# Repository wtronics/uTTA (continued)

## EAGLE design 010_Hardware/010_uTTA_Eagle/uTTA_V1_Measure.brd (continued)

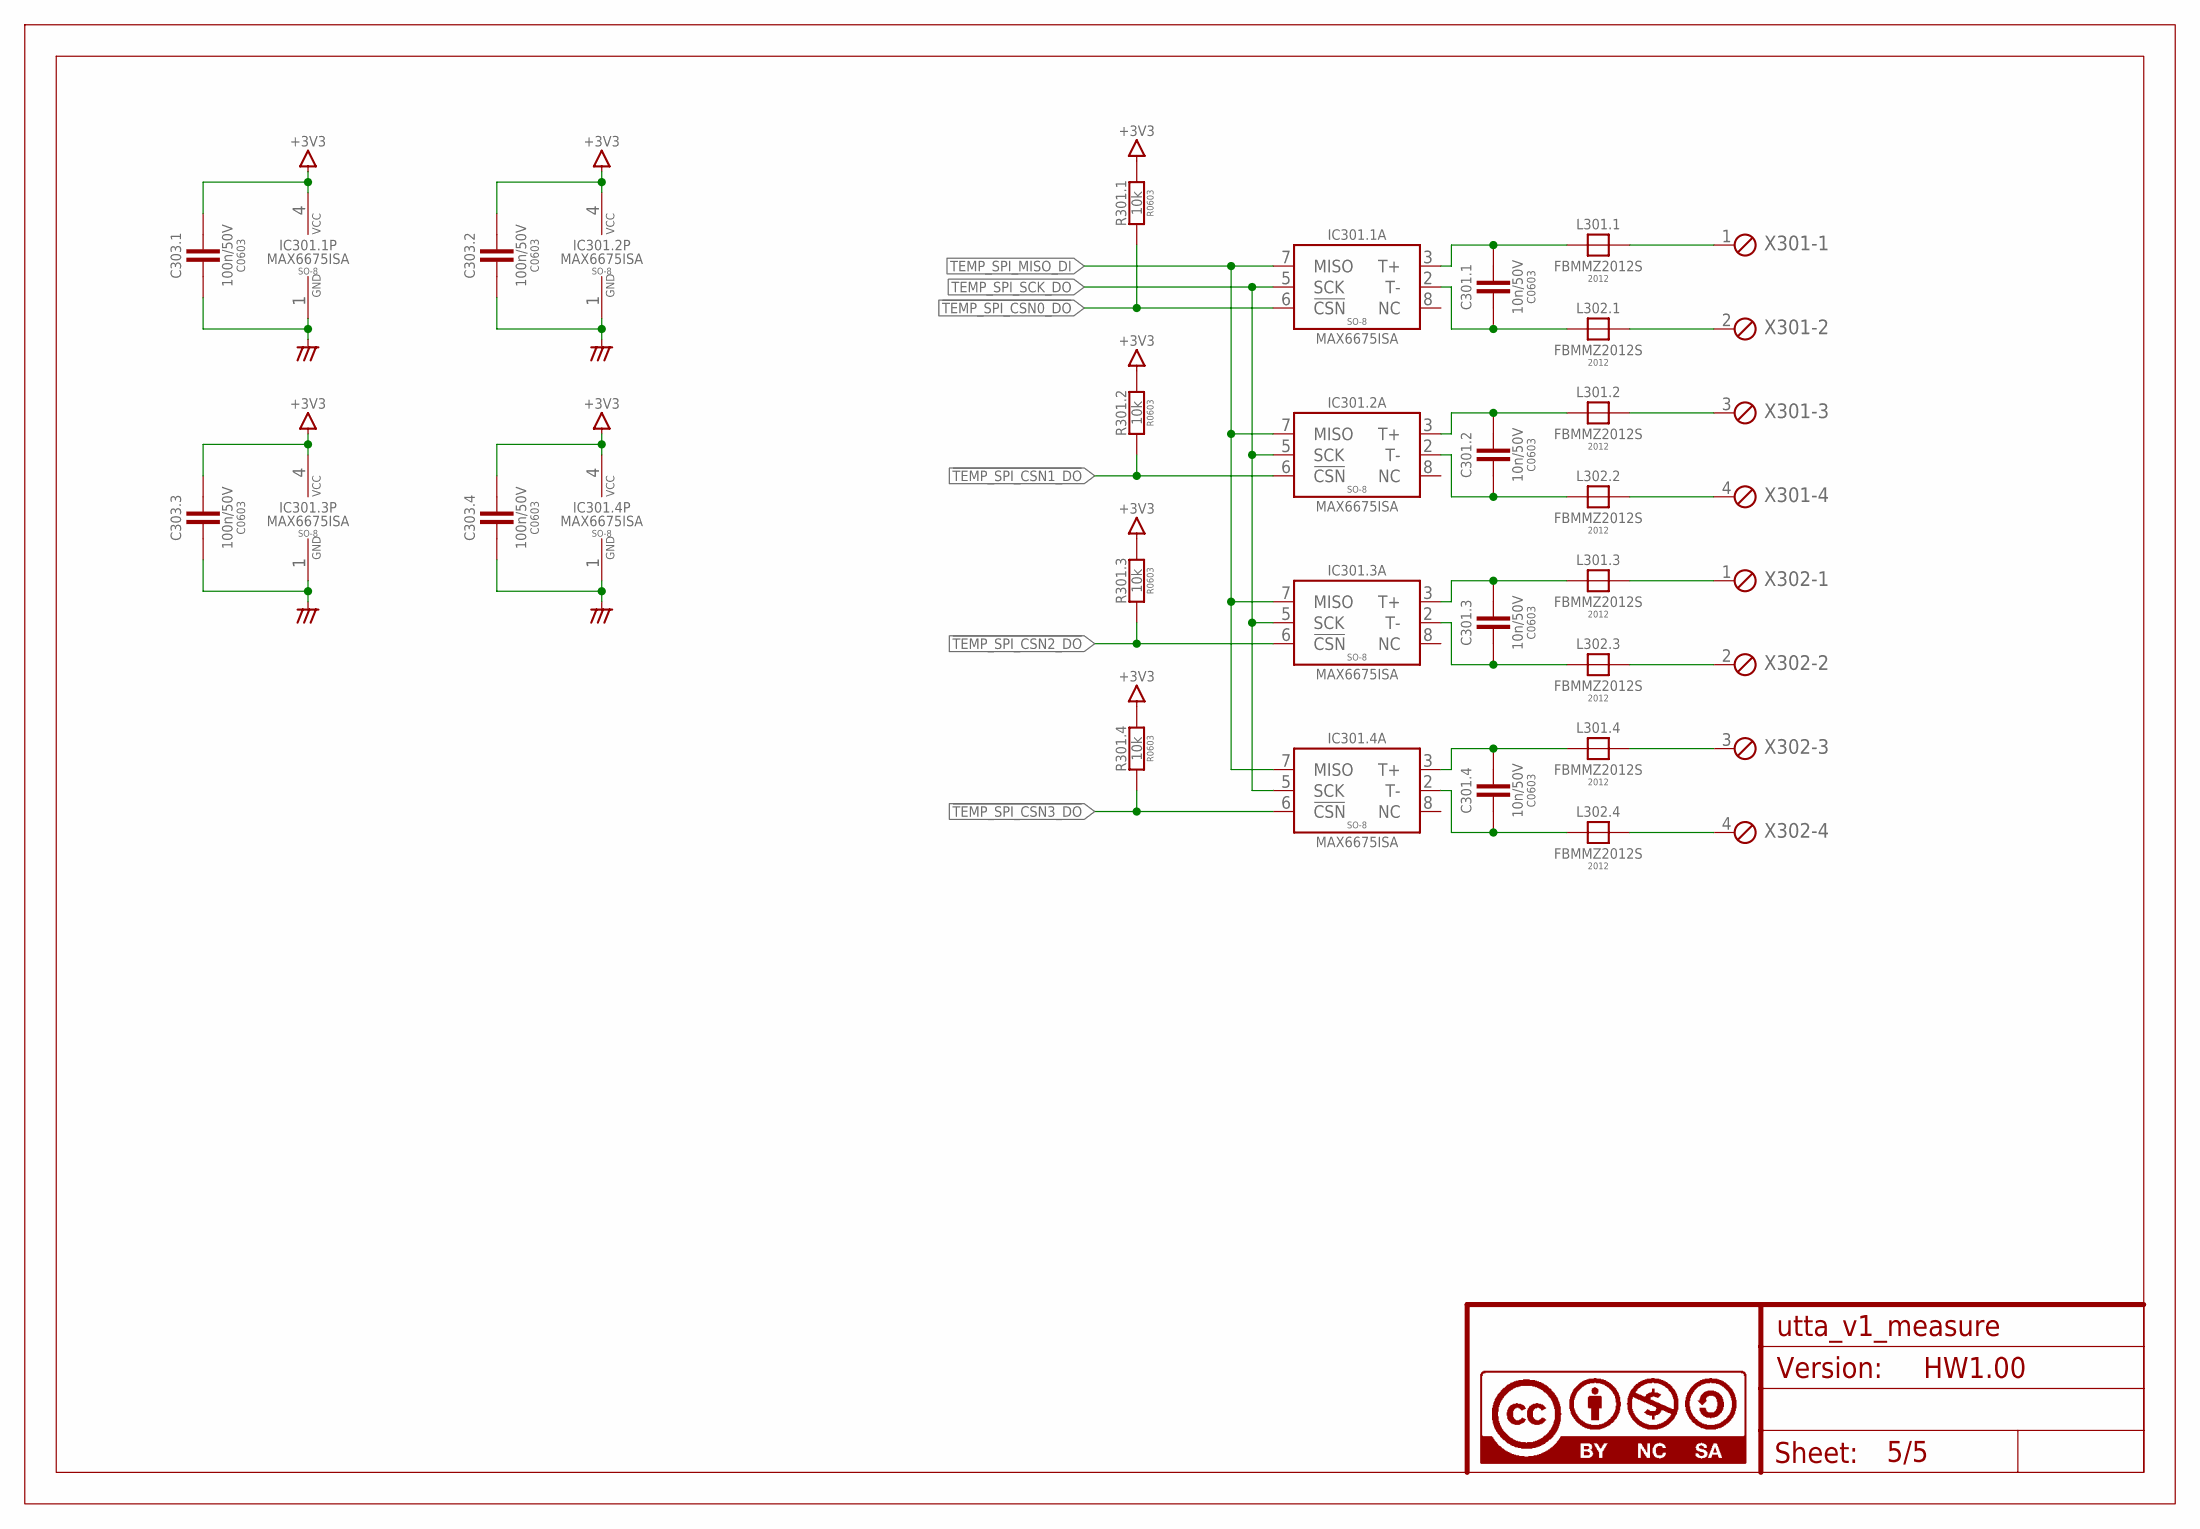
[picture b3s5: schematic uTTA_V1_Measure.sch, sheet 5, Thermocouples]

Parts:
C301.1, C301.2, C301.3, C301.4: 10n/50V; C0603
C303.1, C303.2, C303.3, C303.4: 100n/50V; C0603
IC301.1, IC301.2, IC301.3, IC301.4: MAX6675ISA; SO08
L301.1, L301.2, L301.3, L301.4, L302.1, L302.2, L302.3, L302.4: FBMMZ2012S; FB2012
R301.1, R301.2, R301.3, R301.4: 10k; R0603
U$9: A4L-LOC_CC_BY_NC_SA; A4_LOC_CC_BY_NC_SA
X301, X302: MPT4; 4POL254

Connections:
!TEMP_SPI_CSN0_DO: IC301.1.6 (!CSN), R301.1.2; also elsewhere on the board
!TEMP_SPI_CSN1_DO: IC301.2.6 (!CSN), R301.2.2; also elsewhere on the board
!TEMP_SPI_CSN2_DO: IC301.3.6 (!CSN), R301.3.2; also elsewhere on the board
!TEMP_SPI_CSN3_DO: IC301.4.6 (!CSN), R301.4.2; also elsewhere on the board
+3V3: C303.1.1, C303.2.1, C303.3.1, C303.4.1, IC301.1.4 (VCC), IC301.2.4 (VCC), IC301.3.4 (VCC), IC301.4.4 (VCC), R301.1.1, R301.2.1, R301.3.1, R301.4.1; also elsewhere on the board
AGND: C303.1.2, C303.2.2, C303.3.2, C303.4.2, IC301.1.1 (GND), IC301.2.1 (GND), IC301.3.1 (GND), IC301.4.1 (GND); also elsewhere on the board
TC1+: L301.1.2, X301.1
TC1-: L302.1.2, X301.2
TC2+: L301.2.2, X301.3
TC2-: L302.2.2, X301.4
TC3+: L301.3.2, X302.1
TC3-: L302.3.2, X302.2
TC4+: L301.4.2, X302.3
TC4-: L302.4.2, X302.4
TEMP_SPI_MISO_DI: IC301.1.7 (MISO), IC301.2.7 (MISO), IC301.3.7 (MISO), IC301.4.7 (MISO); also elsewhere on the board
TEMP_SPI_SCK_DO: IC301.1.5 (SCK), IC301.2.5 (SCK), IC301.3.5 (SCK), IC301.4.5 (SCK); also elsewhere on the board
TK1_N: C301.1.2, IC301.1.2 (T-), L302.1.1
TK1_P: C301.1.1, IC301.1.3 (T+), L301.1.1
TK2_N: C301.2.2, IC301.2.2 (T-), L302.2.1
TK2_P: C301.2.1, IC301.2.3 (T+), L301.2.1
TK3_N: C301.3.2, IC301.3.2 (T-), L302.3.1
TK3_P: C301.3.1, IC301.3.3 (T+), L301.3.1
TK4_N: C301.4.2, IC301.4.2 (T-), L302.4.1
TK4_P: C301.4.1, IC301.4.3 (T+), L301.4.1

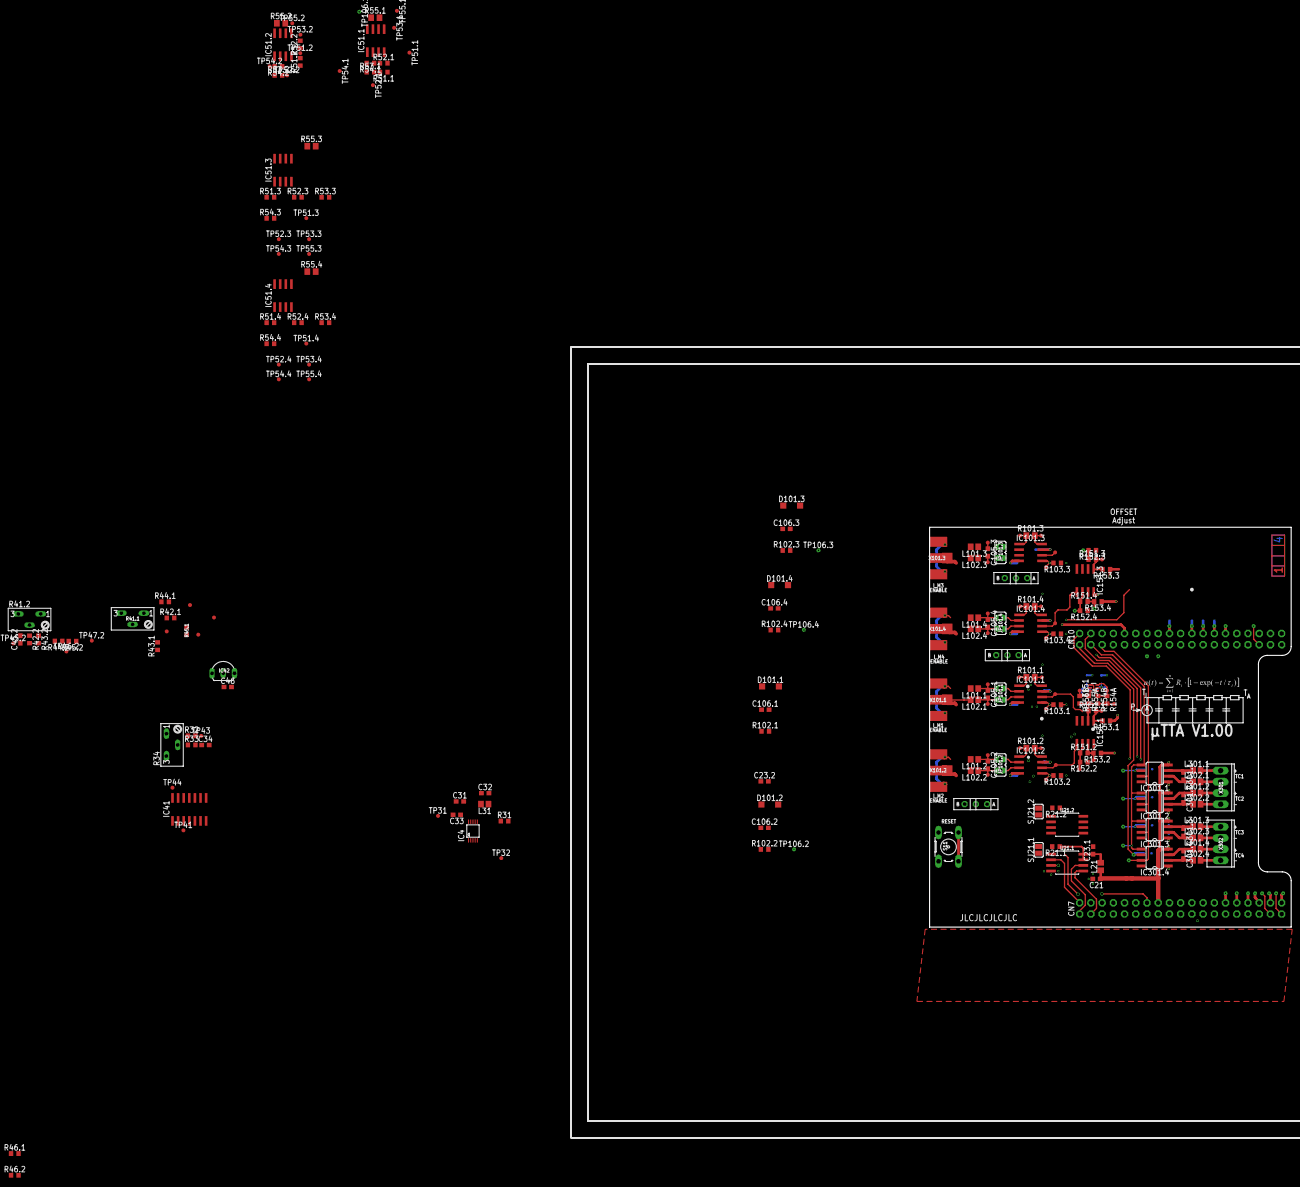
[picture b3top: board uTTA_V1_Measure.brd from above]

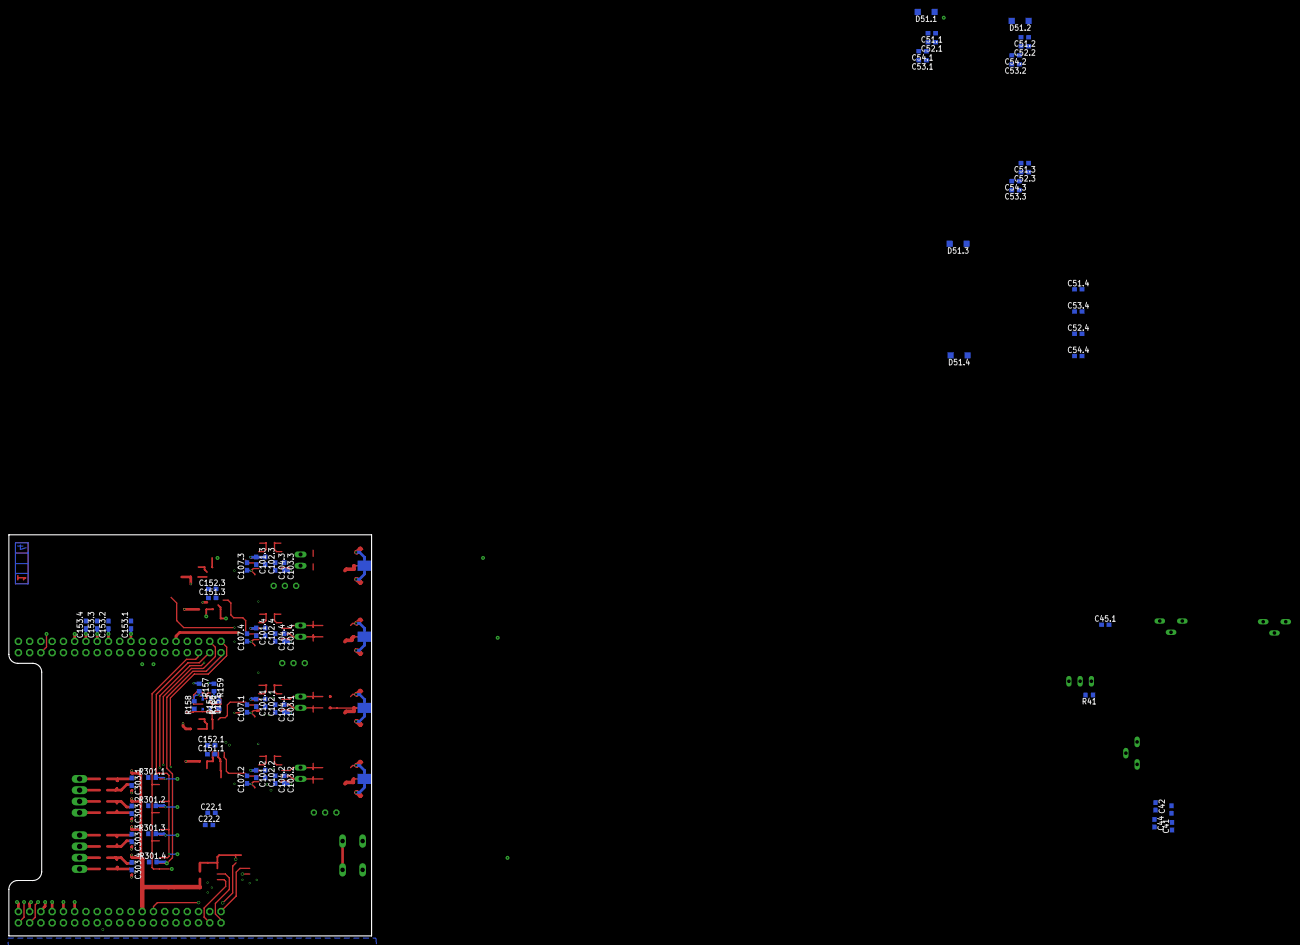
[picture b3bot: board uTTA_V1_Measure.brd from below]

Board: 4 copper layers, 81.8 x 90.5 mm, 313 parts (70 on the bottom side), 140 nets.

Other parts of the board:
U$1: A4_LOC_CC_BY_NC_SA

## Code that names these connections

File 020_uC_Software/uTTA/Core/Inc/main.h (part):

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

// Debug IO1 port
#define DBG_IO1_Pin LL_GPIO_PIN_0
#define DBG_IO1_GPIO_Port GPIOC
// Debug IO2 port
#define DBG_IO2_Pin LL_GPIO_PIN_1
#define DBG_IO2_GPIO_Port GPIOC
// Debug IO3 port
#define DBG_IO3_Pin LL_GPIO_PIN_2
#define DBG_IO3_GPIO_Port GPIOC
// Debug IO4 port
#define DBG_IO4_Pin LL_GPIO_PIN_3
#define DBG_IO4_GPIO_Port GPIOC
// Debug Pin for Sample time generation timer
#define TIM_DBG_PO_Pin LL_GPIO_PIN_10
#define TIM_DBG_PO_GPIO_Port GPIOA
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#define PWSTG_EN_DO_Pin LL_GPIO_PIN_0
#define PWSTG_EN_DO_GPIO_Port GPIOA
// Readback pin of powerstage power supply low
#define PWSTG_UVLO_DI_Pin LL_GPIO_PIN_1
#define PWSTG_UVLO_DI_GPIO_Port GPIOA
// Enable pin of external power supply
#define PSU_EN_DO_Pin LL_GPIO_PIN_4
#define PSU_EN_DO_GPIO_Port GPIOA
// Gate driver power supply enable
#define PWSTG_PWR_EN_DO_Pin LL_GPIO_PIN_0
#define PWSTG_PWR_EN_DO_GPIO_Port GPIOB


// Amplifier Gain Switching outputs
#define GAIN_B0_DO_Pin LL_GPIO_PIN_6
#define GAIN_B0_DO_GPIO_Port GPIOA
#define GAIN_B1_DO_Pin LL_GPIO_PIN_7
#define GAIN_B1_DO_GPIO_Port GPIOA


// Analog inputs for measurement
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#define PGA_DIODE2_AI_GPIO_Port GPIOB
#define PGA_DIODE1_AI_Pin LL_GPIO_PIN_11
#define PGA_DIODE1_AI_GPIO_Port GPIOB
#define CURR_MEAS_AI_Pin LL_GPIO_PIN_14
#define CURR_MEAS_AI_GPIO_Port GPIOB
#define PGA_DIODE4_AI_Pin LL_GPIO_PIN_15
#define PGA_DIODE4_AI_GPIO_Port GPIOB

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
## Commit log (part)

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2025-05-07 Added 6th parametre to SetChannelDescription for CalStatus
2025-05-07 Added Calibration Status to TSP Channels
2025-05-08 Removed dependency to OpenG Toolkit
2025-05-11 Added progress bar
2025-05-11 Update to latest import meta data format
2025-05-12 Added config define EARLY_HW_POWER_BOARD for older hardwares
2025-05-12 Improved localization for numeric conversion
2025-05-12 Improved progress bar behaviour
2025-05-12 Removed outdated parameter from function call
2025-05-12 Changed export setting
2025-05-12 Updated to latest importer return values structure
2025-05-12 Removed unused variables
2025-05-13 Added MetaValue for TSP_Calibration measurements
2025-05-13 Removed unused variable
2025-05-15 Update uTTA_umf_Viewer_GUI.py
    Changed from customtkinter to ttkbootstrap for better styling
    removed unused dependencies
2025-05-19 Fixed bug in state machine
2025-05-19 Added Calibration Measurement indicator flag
2025-05-19 Code Cleanup, added interpolation degrees as variable
2025-05-19 Added error handling for wrong files
2025-05-19 Tweaked file to be recognized as calibration measurement
2025-05-19 Another Try rescaling the window to a matching size
2025-05-26 Bugfix on FIle check
2025-06-13 Changed Frontend to ttkbootstrap
2025-06-13 Removed Customtkinter
2025-06-13 Removed linearization of thermocouple channel
2025-06-16 Updated Examples to latest umf-file version
2025-06-16 change general layout paradigma
2025-06-30 Delete uTTA_umf_Viewer.py
    Outdated because of umf Viewer GUI
2025-06-30 Update uTTA_data_import.py
    Minor bug fixing.
    Moved file selection and handling functions to utta_data_processing
2025-06-30 Complete rewrite to class based approach
    Target:
    - Simplify usage for all applications based on this code
    - Get classes containing all data created for a single measurement
    - Make the processing as standardized as possible throughout the whole toolchain
2025-06-30 Update uTTA_Deconvolution_LucyRichardson_file.py
    updated to class based processing library
2025-06-30 Update uTTA_Postprocess_Calibration_GUI_v2.py
    Updated processing to class based approach to simplify usage
2025-06-30 Update uTTA_Postprocess_Measurement.py
    Moved all measurement post processing into utta_processing class
2025-06-30 Update uTTA_umf_Viewer_GUI.py
    Moved all calculations into uTTAZthProcessing class to unify calculations
2025-06-30 Update uTTA_umf_Viewer_GUI.py
    Added general style settings for the plot
2025-06-30 Update uTTA_umf_Viewer_GUI.py
    Changed window size.
    Optimized scaling of plots for better scaling on different screens
2025-06-30 Bugfix
    replaced duplicate voltage plot in 1,1 with current plot
2025-08-05 Added VIs to get and updae uTTA System Time
2025-08-05 Added the System Time Update Feature
2025-08-27 Delete uTTA_V1_Lower_Housing.3mf
    Removal because of outdated design
2025-08-27 New housing design to fit all PCBs into one housing
2025-08-30 Updated images
2025-09-01 Swapped LEDs LED1 and LED3 because of twisted naming
2025-09-01 Added Configuration Parameters
    Added new configuration parameters (HW_MEASURE_BOARD_BELOW_V2P2 and ENABLE_TIMER_DEBUGGING) for better configurability between buggy HW Revisions.
    Moved "End User Configurable" Parameters to top of file.
2025-09-01 Moved Pin Configurations to configuration_parameters.h
2025-09-01 Added Configuration Cases for GPIOs
2025-09-01 Added Features & Bugfix
    Added Status LED outputs
    Hopefully fixed bug with ADC & DMA on repeated measurements
2025-09-01 Added Export Functions to TDIM-Master and Zth-Curve
2025-09-01 Updated to latest utta_data_processing version
2025-09-01 Optimized plot layout
2025-09-01 Changed Subplot contents
2025-09-05 Optimized Zth Export
    Optimized export to have at least the full decadic steps (1 10 100 etc) in the export
2025-09-05 Made DUT Name field larger
2025-09-05 Update uTTA_SetDUT_Name.vi
    Added Global Settings variable to adjust the max length of the DUT Name
2025-09-05 Update uTTA_SetCH_Description.vi
    Introduced Global settings variable to set the max length of the channel name
2025-09-05 Update uTTA_Read_File_UI.vi
    Improved user experience
2025-09-05 Update config_parameters.h
    Added configuration define for MAX_DUT_NAME_LENGTH and CHANNEL_NAME_MAX_LENGTH
2025-09-06 Update uTTA_data_import.py
    Added function to check if the block length of the adc and find block with missing samples
2025-09-07 Update to new data structures
    Tried to remove usage of dictionaries as main data structures
2025-09-08 Update uTTA_data_processing.py
    Aded functions to load and save configuration parameters from an ini-file
2025-09-08 no change
2025-09-18 Added identifier in file for device name
2025-09-18 Added readouts for device name and file version
2025-09-18 Improved detection of file extension
2025-09-18 Update to latest file version specification
2025-09-28 Moved files to library folder
2025-09-28 Updated library dependencies
2025-09-28 Renamed to .pyw and updated library dependencies
2025-09-28 Moved to Libraries Folder. Improved Plotting capabilities
2025-09-30 Added new settings parameters, added commenting on interpolation calculation
2025-09-30 Added settings to settings-tab.
2025-09-30 Renamed calibration mode
2025-09-30 Moved content of settings tab to separate widget class
2025-09-30 Moved Frame for clearer layout
2025-09-30 Removed unused settings_changed function
2025-09-30 Added settings for semiconductor properties
2025-09-30 Reorganized Flags
2025-09-30 Added parameters for storage in config file
2025-09-30 Added frame for future parameters to be stored
2025-09-30 Removed hardcoding of Ratio Method
2025-09-30 Fixed typo in read in of spinbox
2025-09-30 Added missing type conversion
2025-10-02 Fixed library dependency
2025-10-02 Updated library version dependency
2025-10-02 Update of version for next release
2025-10-02 Update README.md
    Updated achivements
2025-10-04 Created Logo for utta
2025-10-04 Code cleanup, started adding report function
2025-10-04 started adding report feature
2025-10-04 fixed wrong configuraion of configparser
    new settings destroyed case sensitive keys
2025-10-06 Added CalStatus Description
2025-10-19 Fixed interpolation method
2025-10-19 Little variable cleanup to get rid of global variables (just 3 left for debugging purpose)
2025-10-19 Added new displaying option to show the full tangent within the interpolation window
2025-10-19 Added Error Handling on Plot Axis
    Added Error Handling when log plots contains negative values. In this case the Y-Axis scaling is switched to linear mode
2025-10-19 Added automatic error handling for negative values on log Y-Axis
2025-10-19 Increased default average half width
2025-11-02 Change property names to get rid of complains by pylance
2025-11-02 Update to mnemonics of latest ttkbootstrap version
2025-11-03 Fixed formatting of Zth Export
2025-11-03 Fixed exported data
    raw adc values were exported instead of the zth curve
2025-11-11 Deleted useless files
2025-11-11 removed debug statement
2025-11-11 Moved file to library folder
2025-11-11 Moved file to library
2025-11-11 Updated library dependency
2025-11-11 Added tksheet to dependencies
2025-11-16 Added safety question to prevent unintended deletion of calibration file.
2025-11-16 Added new button to export t3i intermediate file
2025-11-22 Update to Revision 2.5.3
    Changed values of resistors for optocouplers (reduced LED current). Replaced 10 ohm input resistors with 0Ohm
2025-11-22 changed resistor values
    Changed Values of R101 and R102 to 0 Ohm
    Changed value of R108 from 100 Ohm to 240 Ohm (to reduce optocoupler LED current)
    Changed value of R110 from 220 Ohm to 470 Ohm (to reduce LED current)
2025-11-22 Updated assembly drawings to match BOM
2025-11-22 Rename uTTA_V2.2_Power.sch to uTTA_V2.5.3_Power.sch
2025-11-22 Rename uTTA_Measure_V2.5.3_Assembly.pdf to uTTA_Power_V2.5.3_Assembly.pdf
2025-11-22 Rename uTTA_V2.5.3_Power.pdf to uTTA_Power_V2.5.3.pdf
2025-11-27 Fixed minor issues in LV GUI
2026-01-04 removed outdated variants from design
2026-01-04 Added missing response header
2026-01-04 Clean up of frontpanel controls arrangement
2026-01-04 Rename uTTA_V2.2_Measure.brd to uTTA_Measure.brd
2026-01-04 Rename uTTA_V2.2_Measure.sch to uTTA_Measure.sch
2026-01-04 Rename uTTA_V2.2_SystemDrawings.sch to uTTA_SystemDrawings.sch
2026-01-04 Rename uTTA_V2.5.3_Power.sch to uTTA_Power.sch
2026-01-04 Rename uTTA_Measure_V2.2.pdf to uTTA_Measure.pdf
2026-01-04 Rename uTTA_Measure_V2.2_Assembly.pdf to uTTA_Measure_Assembly.pdf
2026-01-04 Rename uTTA_Power_V2.5.3.pdf to uTTA_Power.pdf
2026-01-04 Rename uTTA_Power_V2.5.3_Assembly.pdf to uTTA_Power_Assembly.pdf
2026-01-04 Rename uTTA_V2.2_Measure.csv to uTTA_Measure.csv
2026-01-04 Rename uTTA_V2.2_Power.csv to uTTA_Power.csv
2026-01-06 Removed unneccessary outputs on serial terminal
2026-01-06 Added output in case a calibration file is available
2026-01-06 Bugfix on detection of file exits (wrong comparison)
2026-01-07 Update of Frontpanel Control Arrangement
2026-01-11 Tied buffer length to length of SCPI serial buffer
2026-01-11 Added uTTA Serial Port Driver in Python
2026-03-13 Improved scalability of window.
2026-03-13 Placement & Style Improvements
    Changed placement from grid to pack.
    Added Axis labels on x-Axis for every decade
2026-03-13 Improved window styling
    Changed widget placement from grid to pack
2026-03-16 Improved string formatting to f-strings
2026-03-18 Added support for logging
2026-03-18 Added support for logging + Bugfix
    Bugfixed coupling calculation. Calculation results were switching signedness after each change in the interpolation window
2026-03-18 Added logging support
    Removed old print to console statements and replaced them by logger statements
2026-03-18 Added Logging support and Documentation
2026-03-29 Increased Max UART Buffer length (just for safety)
2026-03-29 Change from sprintf to snprintf
    Changed to snprintf to prevent the system from buffer overflow.
2026-03-29 Added continious checking of the gatedriver supply during measurement.
2026-04-05 Added new state to create measurement file after inital checks
2026-04-05 Adapted measurement routine to new state
2026-06-04 Fixed wrong index
2026-06-04 improved the use of no_gui
2026-06-04 Update the way the current channel is treated. Played around with lucy richardson deconvolution
2026-06-04 Adapted variable names after change in utta_data_processing
2026-06-04 Added Logging functionality
2026-06-04 New widget to be used in future projects
2026-06-04 Added file header
2026-06-04 Added file headers
2026-06-04 Fixed variable names after change in utta_data_processing
2026-06-05 Finally added some commenting on functions
2026-06-05 Improved documentation
    Added file header
    Added docstrings to all functions
    Replaced .format() with f-strings
2026-06-09 Added docstrings to functions
2026-06-23 Added documentation
2026-06-23 Added documentation for every function
2026-06-24 Standardized docstrings to a common format
2026-06-26 Reactivated the style
2026-06-26 Changed API
    Changed API of engine a little. Now the plots are mapped by using a mapping function. Furthermore, the plots position is defined by row and column instead of a bare array index.
    Now it is possible to remove or add columns and rows on runtime!
2026-06-26 Removed bug added new plotting API
    Removed outdated function.
    Implemented new plotting API
2026-06-26 Adaption to new Plotting API
2026-06-26 Improved behavior of plotting
2026-06-27 Update to more flexible window sizes
2026-06-28 Update uTTA_data_processing.py
    Started adding docstrings to all functions
    Fixed wrong assignments of data to plots.
    Rebuild function find_static_states. The old one was quite crappy.
2026-06-28 Update uTTA_Postprocess_Calibration_GUI.pyw
    Added settings tab to user menu.
    Tool configuration is now saved in a new ini-file
    Tool configuration is restored on restart.
2026-06-28 Update uTTA_Zth_Comparison_GUI.pyw
    Improved Window appearance
2026-06-28 Added Documentation and Docstrings
2026-06-29 Added custom formatting to tables
    Added a new custom formatting to tksheet table to have values with SI-units in there
2026-06-29 Added hide/unhide feature for plots
2026-06-30 Bugfix of variable names which were forgotten to be changed
2026-06-30 Added Parameter for root-Window
2026-06-30 Added Section for Images
2026-06-30 Added image section to report
